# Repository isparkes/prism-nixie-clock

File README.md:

# Prism Large Tube Nixie Clock
This is the board design for the "Prism" 6-digit Nixie Clock based on the ESP-8266 with NeoPixel LED backlights

## Links
This code comes from:       https://bitbucket.org/isparkes/prism-firmware/
The Hardware:               https://bitbucket.org/isparkes/prism-direct-drive-in-18/

My Shop:                    https://www.nixieclock.biz/Store.html
Manuals:                    https://www.nixieclock.biz/Manuals.html

#### Features:
- Open source Hard and Software 
- Internet connected with the ESP8266
- Real Time Clock interface for backup
- Configuration stored in EEPROM
- RGB Back lighting
- Automatic linear dimming using light sensor

**Instruction and User Manuals (including schematic) can be found at:** [https://www.nixieclock.biz/Manuals.html](https://www.nixieclock.biz/Manuals.html)

You can buy this from: [https://www.nixieclock.biz/Store.html](https://www.nixieclock.biz/Store.html)

YouTube channel: [Ian's YouTube Channel](https://www.youtube.com/channel/UCiC34G8yl0mN2BK-LzPw0ew?view_as=subscriber)

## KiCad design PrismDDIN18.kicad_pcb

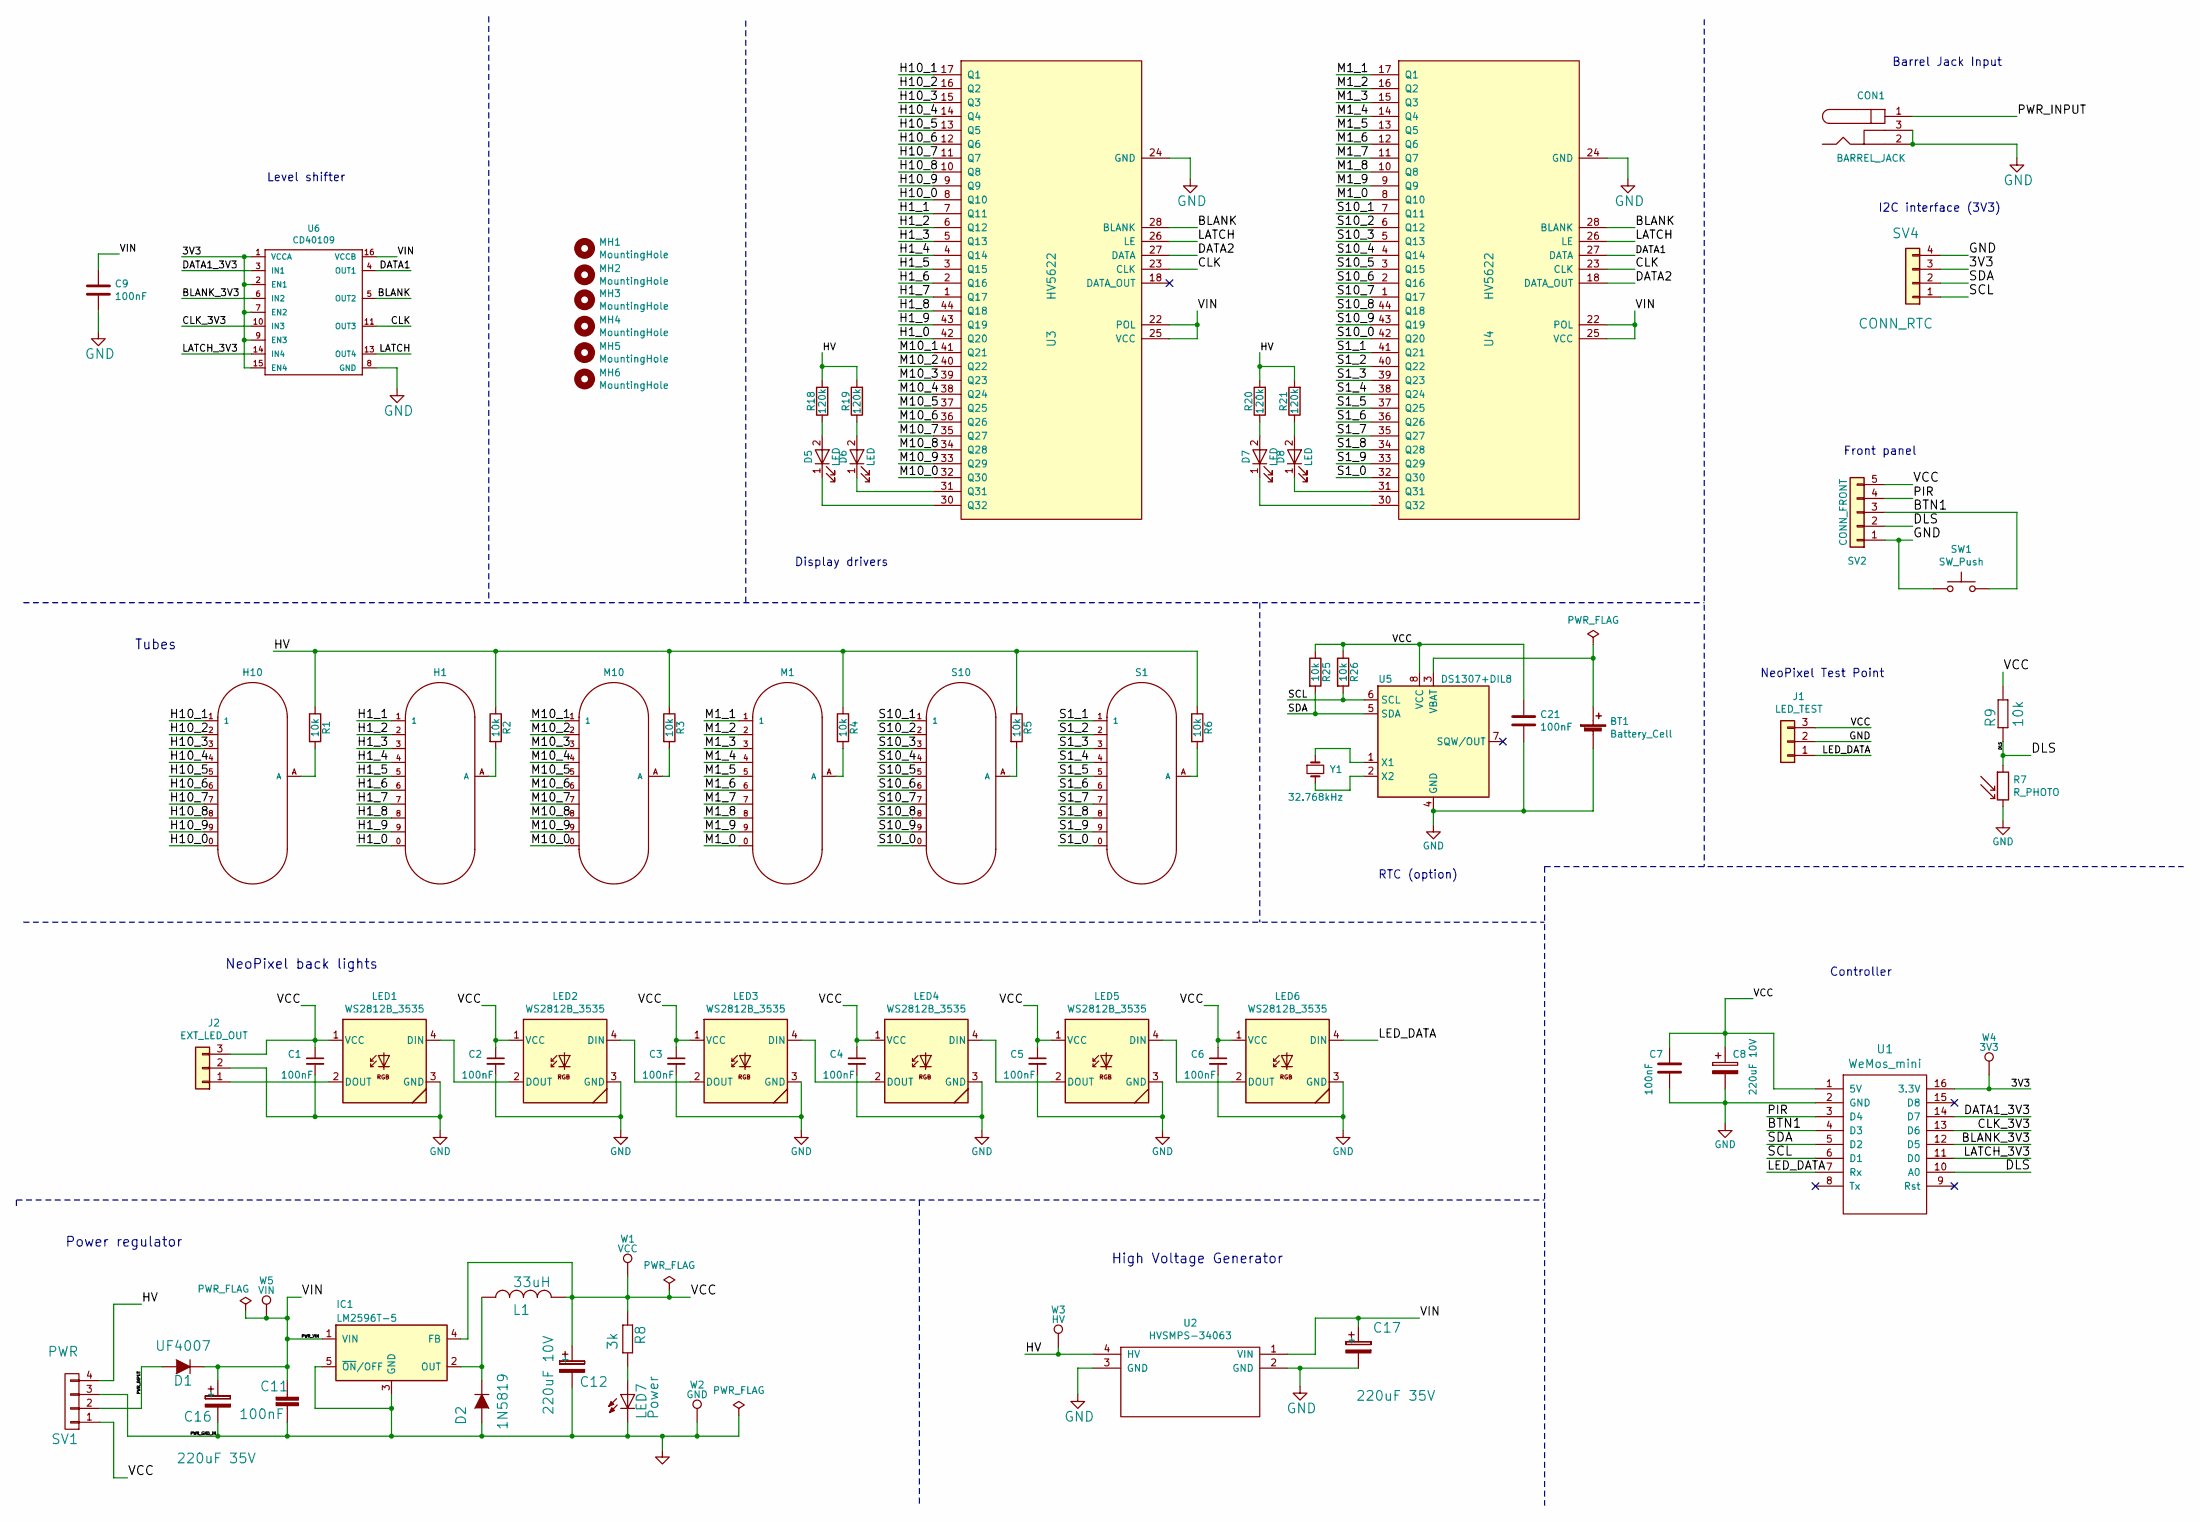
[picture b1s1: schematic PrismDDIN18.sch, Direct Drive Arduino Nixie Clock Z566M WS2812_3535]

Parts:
BT1: Battery_Cell; CR1220-CoinCell
C1, C2, C3, C4, C5, C6: 100nF; C_1206_3216Metric
C7, C9, C11, C21: 100nF; C025-024X044
C8, C12: 220uF 10V; C_Radial_D6.3_L11.2_P2.5
C16, C17: 220uF 35V; C_Radial_D6.3_L11.2_P2.5
CON1: BARREL_JACK
D1: UF4007; Diode_DO-41_1N4001
D2: 1N5819; Diode_DO-41_1N4001
D5, D6, D7, D8: LED; LED-5MM-Centred
H1, H10: Z566M; IN-18-standoff-pins
IC1: LM2596T-5; TO220-5A_H
J1: LED_TEST; Header_MA03-1_Small
J2: EXT_LED_OUT; Header_MA03-1_Small
L1: 33uH; Inductor-33mH-TH-SMD
LED1, LED2, LED3, LED4, LED5, LED6: WS2812B_3535; WS2812B-SmallPads
LED7: Power; LED_3MM
M1, M10: Z566M; IN-18-standoff-pins
MH1, MH2, MH3, MH4, MH5, MH6: MountingHole; MountingHole_3.2mm_M3
R1, R2, R3, R4, R5, R6: 10k; R_Short_P7.62mm_Horizontal
R7: R_PHOTO; C_Naked
R8: 3k; R-0207_2V
R9, R25, R26: 10k; R-0207_2V
R18, R19, R20, R21: 120k; R_Short_P7.62mm_Horizontal
S1, S10: Z566M; IN-18-standoff-pins
SV1: PWR; Header_MA04-1
SV2: CONN_FRONT; Header_MA05-1
SV4: CONN_RTC; Header_MA04-1
SW1: SW_Push; SW_SPST_CK_RS282G05A3
U1: WeMos_mini; WeMos_D1_mini_board_simple
U2: HVSMPS-34063
U3, U4: HV5622; PLCC44
U5: DS1307+DIL8; DIP-8_W7.62mm
U6: CD40109; DIP-16_W7.62mm
W1: VCC; TESTPAD_P1-13
W2: GND; TESTPAD_P1-13
W3: HV; TESTPAD_P1-13
W4: 3V3; TESTPAD_P1-13
W5: VIN; TESTPAD_P1-13
Y1: 32.768kHz; Crystal_DS10_d1.0mm_l4.3mm_Horizontal

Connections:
/3V3: SV4.3, U1.16 (3.3V), U6.1 (VCCA), U6.2 (EN1), U6.7 (EN2), U6.9 (EN3), U6.15 (EN4), W4.1
/BLANK: U3.28 (BLANK), U4.28 (BLANK), U6.5 (OUT2)
/BLANK_3V3: U1.12 (D5), U6.6 (IN2)
/BTN1: SV2.3, SW1.2, U1.4 (D3)
/CLK: U3.23 (CLK), U4.23 (CLK), U6.11 (OUT3)
/CLK_3V3: U1.13 (D6), U6.10 (IN3)
/DATA1: U4.27 (DATA), U6.4 (OUT1)
/DATA1_3V3: U1.14 (D7), U6.3 (IN1)
/DATA2: U3.27 (DATA), U4.18 (DATA_OUT)
/DLS: R7.1, R9.1, SV2.2, U1.10 (A0)
/H1_0: H1.0, U3.42 (Q20)
/H1_1: H1.1, U3.7 (Q11)
/H1_2: H1.2, U3.6 (Q12)
/H1_3: H1.3, U3.5 (Q13)
/H1_4: H1.4, U3.4 (Q14)
/H1_5: H1.5, U3.3 (Q15)
/H1_6: H1.6, U3.2 (Q16)
/H1_7: H1.7, U3.1 (Q17)
/H1_8: H1.8, U3.44 (Q18)
/H1_9: H1.9, U3.43 (Q19)
/H10_0: H10.0, U3.8 (Q10)
/H10_1: H10.1, U3.17 (Q1)
/H10_2: H10.2, U3.16 (Q2)
/H10_3: H10.3, U3.15 (Q3)
/H10_4: H10.4, U3.14 (Q4)
/H10_5: H10.5, U3.13 (Q5)
/H10_6: H10.6, U3.12 (Q6)
/H10_7: H10.7, U3.11 (Q7)
/H10_8: H10.8, U3.10 (Q8)
/H10_9: H10.9, U3.9 (Q9)
/HV: R1.1, R2.1, R3.1, R4.1, R5.1, R6.1, R18.2, R19.2, R20.2, R21.2, SV1.4, U2.4 (HV), W3.1
/LATCH: U3.26 (LE), U4.26 (LE), U6.13 (OUT4)
/LATCH_3V3: U1.11 (D0), U6.14 (IN4)
/LED_DATA: J1.1, LED6.4 (DIN), U1.7 (Rx)
/M1_0: M1.0, U4.8 (Q10)
/M1_1: M1.1, U4.17 (Q1)
/M1_2: M1.2, U4.16 (Q2)
/M1_3: M1.3, U4.15 (Q3)
/M1_4: M1.4, U4.14 (Q4)
/M1_5: M1.5, U4.13 (Q5)
/M1_6: M1.6, U4.12 (Q6)
/M1_7: M1.7, U4.11 (Q7)
/M1_8: M1.8, U4.10 (Q8)
/M1_9: M1.9, U4.9 (Q9)
/M10_0: M10.0, U3.32 (Q30)
/M10_1: M10.1, U3.41 (Q21)
/M10_2: M10.2, U3.40 (Q22)
/M10_3: M10.3, U3.39 (Q23)
/M10_4: M10.4, U3.38 (Q24)
/M10_5: M10.5, U3.37 (Q25)
/M10_6: M10.6, U3.36 (Q26)
/M10_7: M10.7, U3.35 (Q27)
/M10_8: M10.8, U3.34 (Q28)
/M10_9: M10.9, U3.33 (Q29)
/PIR: SV2.4, U1.3 (D4)
/PWR_INPUT: CON1.1, D1.2 (A), SV1.2
/PWR_VIN: C9.1, C11.2, C16.1, C17.1, D1.1 (K), IC1.1 (VIN), U2.1 (VIN), U3.22 (POL), U3.25 (VCC), U4.22 (POL), U4.25 (VCC), U6.16 (VCCB), W5.1
/S1_0: S1.0, U4.32 (Q30)
/S1_1: S1.1, U4.41 (Q21)
/S1_2: S1.2, U4.40 (Q22)
/S1_3: S1.3, U4.39 (Q23)
/S1_4: S1.4, U4.38 (Q24)
/S1_5: S1.5, U4.37 (Q25)
/S1_6: S1.6, U4.36 (Q26)
/S1_7: S1.7, U4.35 (Q27)
/S1_8: S1.8, U4.34 (Q28)
/S1_9: S1.9, U4.33 (Q29)
/S10_0: S10.0, U4.42 (Q20)
/S10_1: S10.1, U4.7 (Q11)
/S10_2: S10.2, U4.6 (Q12)
/S10_3: S10.3, U4.5 (Q13)
/S10_4: S10.4, U4.4 (Q14)
/S10_5: S10.5, U4.3 (Q15)
/S10_6: S10.6, U4.2 (Q16)
/S10_7: S10.7, U4.1 (Q17)
/S10_8: S10.8, U4.44 (Q18)
/S10_9: S10.9, U4.43 (Q19)
/SCL: R26.2, SV4.1, U1.6 (D1), U5.6 (SCL)
/SDA: R25.2, SV4.2, U1.5 (D2), U5.5 (SDA)
/VCC: C1.1, C2.1, C3.1, C4.1, C5.1, C6.1, C7.1, C8.1, C12.1, C21.1, IC1.4 (FB), J1.3, J2.3, L1.2, LED1.1 (VCC), LED2.1 (VCC), LED3.1 (VCC), LED4.1 (VCC), LED5.1 (VCC), LED6.1 (VCC), R8.1, R9.2, R25.1, R26.1, SV1.1, SV2.5, U1.1 (5V), U5.8 (VCC), W1.1
GND: BT1.2 (-), C1.2, C2.2, C3.2, C4.2, C5.2, C6.2, C7.2, C8.2, C9.2, C11.1, C12.2, C16.2, C17.2, C21.2, CON1.2, CON1.3, D2.2 (A), IC1.3 (GND), IC1.5 (~ON~/OFF), J1.2, J2.2, LED1.3 (GND), LED2.3 (GND), LED3.3 (GND), LED4.3 (GND), LED5.3 (GND), LED6.3 (GND), LED7.K (C), R7.2, SV1.3, SV2.1, SV4.4, SW1.1, U1.2 (GND), U2.2 (GND), U2.3 (GND), U3.24 (GND), U4.24 (GND), U5.4 (GND), U6.8 (GND), W2.1
unnamed: BT1.1 (+), U5.3 (VBAT)
unnamed: D2.1 (K), IC1.2 (OUT), L1.1
unnamed: D5.1 (K), U3.30 (Q32)
unnamed: D5.2 (A), R18.1
unnamed: D6.1 (K), U3.31 (Q31)
unnamed: D6.2 (A), R19.1
unnamed: D7.1 (K), U4.30 (Q32)
unnamed: D7.2 (A), R20.1
unnamed: D8.1 (K), U4.31 (Q31)
unnamed: D8.2 (A), R21.1
unnamed: H1.A, R2.2
unnamed: H10.A, R1.2
unnamed: J2.1, LED1.2 (DOUT)
unnamed: LED1.4 (DIN), LED2.2 (DOUT)
unnamed: LED2.4 (DIN), LED3.2 (DOUT)
unnamed: LED3.4 (DIN), LED4.2 (DOUT)
unnamed: LED4.4 (DIN), LED5.2 (DOUT)
unnamed: LED5.4 (DIN), LED6.2 (DOUT)
unnamed: LED7.A, R8.2
unnamed: M1.A, R4.2
unnamed: M10.A, R3.2
unnamed: R5.2, S10.A
unnamed: R6.2, S1.A
unnamed: U5.1 (X1), Y1.1
unnamed: U5.2 (X2), Y1.2

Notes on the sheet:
Power regulator
RTC (option)
Barrel Jack Input
High Voltage Generator
NeoPixel back lights
Tubes
Display drivers
I2C interface (3V3)
Front panel
NeoPixel Test Point
Level shifter
Controller

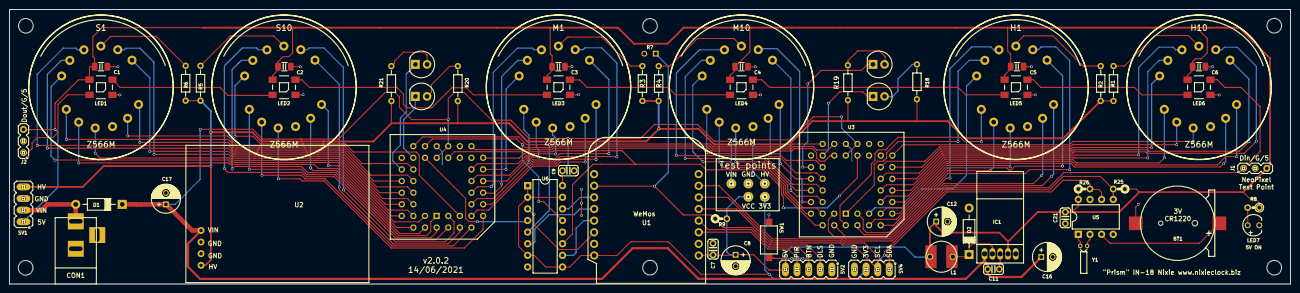
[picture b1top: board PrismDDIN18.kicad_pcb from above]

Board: 2 copper layers, 280.0 x 60.0 mm, 76 parts (1 on the bottom side), 106 nets.

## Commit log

2018-11-11 First version
2018-11-22 Update to KiCAD 5, re-space
2018-11-22 Shrink board to 280x60
2018-11-23 Added DS1307, re-laid out HV
2018-11-23 Align tubes, add mounting holes
2018-11-24 Initial Wemos version
2018-11-25 Improve VCC and HV layout
2018-11-25 More minor improvements
2018-11-25 "Balance" HV chips
2018-11-26 Update IN-18 footprints, define RV1 value
2018-12-12 Re-center connections to tubes
2018-12-12 Add 3V3 test point, move test points
2018-12-20 Add I2C pullups
2019-01-04 Minor adjustments to level shifter placings
2019-02-07 Correct 2N3906 pin out
2019-02-26 Update component values
2019-02-26 Add centre mouting hole
2019-02-26 Update netlist, bodard date
2019-08-28 correct LV inductor value
2019-08-28 Contribution from Hartmut with sk6812 mini
2020-01-31 Use APA106
2020-03-02 License
2021-06-16 Update to new layout
2021-10-05 Rotate tubes
2021-10-17 Change pin size of socket, swap D0 and D5 for PWM blanking
2021-10-18 Prepare for FAB
2023-07-10 Ignore ZIPs
